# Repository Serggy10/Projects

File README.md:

# Projects
This folder contains projects I have been working on, including plans and designs in Autodesk Autocad and Inventor, PCB designs using Kicad, software development for Arduino/ESP32 using Visual Studio Code in C++, Android Studio and others.

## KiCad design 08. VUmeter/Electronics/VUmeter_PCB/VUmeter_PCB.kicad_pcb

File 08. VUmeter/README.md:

# Description
This project is based on the idea of a LED strip that reacts to sound. Controlled by an ESP32 and interacting with Alexa. Work in progress. Based on these ideas:

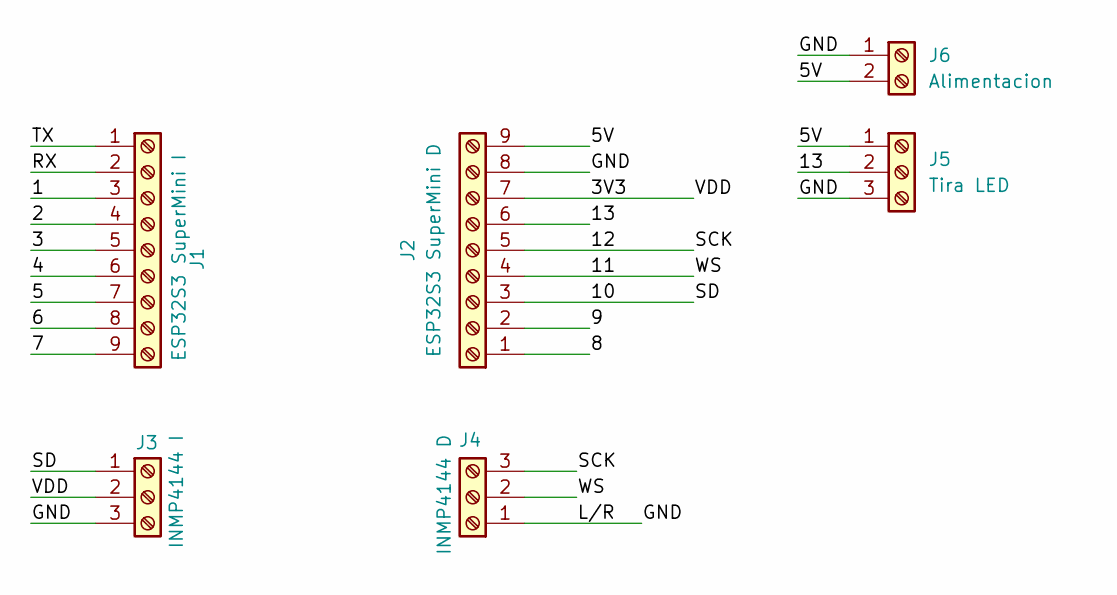
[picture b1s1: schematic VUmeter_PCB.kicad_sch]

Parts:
J1: ESP32S3 SuperMini I; PinHeader_1x09_P2.54mm_Vertical
J2: ESP32S3 SuperMini D; PinHeader_1x09_P2.54mm_Vertical
J3: INMP4144 I; PinHeader_1x03_P2.54mm_Vertical
J4: INMP4144 D; PinHeader_1x03_P2.54mm_Vertical
J5: Tira LED; PinHeader_1x03_P2.54mm_Vertical
J6: Alimentacion; PinHeader_1x02_P2.54mm_Vertical

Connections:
/1: J1.3
/2: J1.4
/3: J1.5
/3V3: J2.7, J3.2
/4: J1.6
/5: J1.7
/5V: J2.9, J5.1, J6.2
/6: J1.8
/7: J1.9
/8: J2.1
/9: J2.2
/10: J2.3, J3.1
/11: J2.4, J4.2
/12: J2.5, J4.3
/13: J2.6, J5.2
/GND: J2.8, J3.3, J4.1, J5.3, J6.1
/RX: J1.2
/TX: J1.1

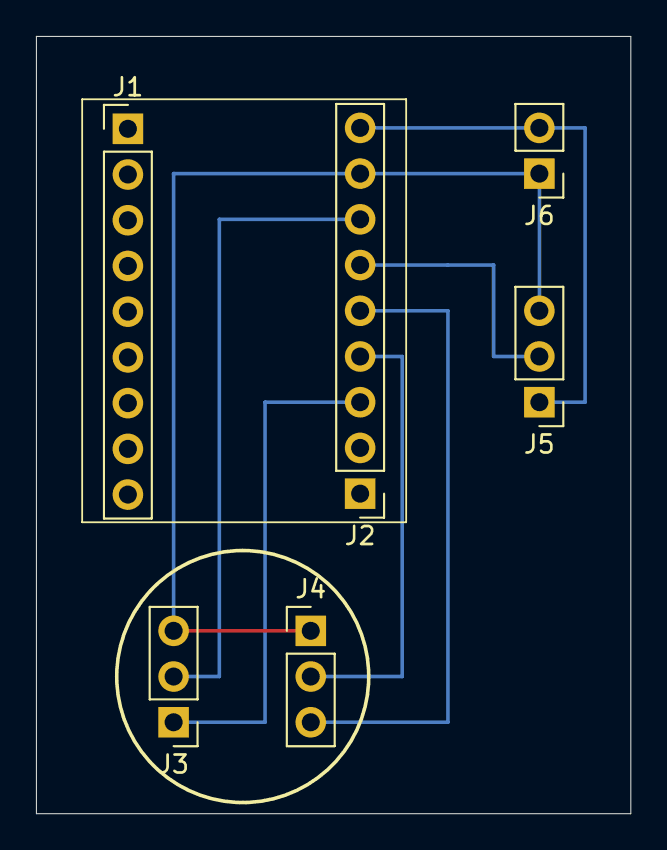
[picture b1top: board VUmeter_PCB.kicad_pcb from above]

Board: 2 copper layers, 33.0 x 43.2 mm, 6 parts (0 on the bottom side), 7 nets.

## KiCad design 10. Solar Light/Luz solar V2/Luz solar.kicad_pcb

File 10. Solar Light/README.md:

# Description IC
This project was born out of the poor quality of solar lights on the market. It uses a lithium-ion battery and a DW01A IC to manage the charge and discharge. The charging is done by a solar cell through a CN3163 IC. A video of it working can be found in the Resources folder. Work in progress.

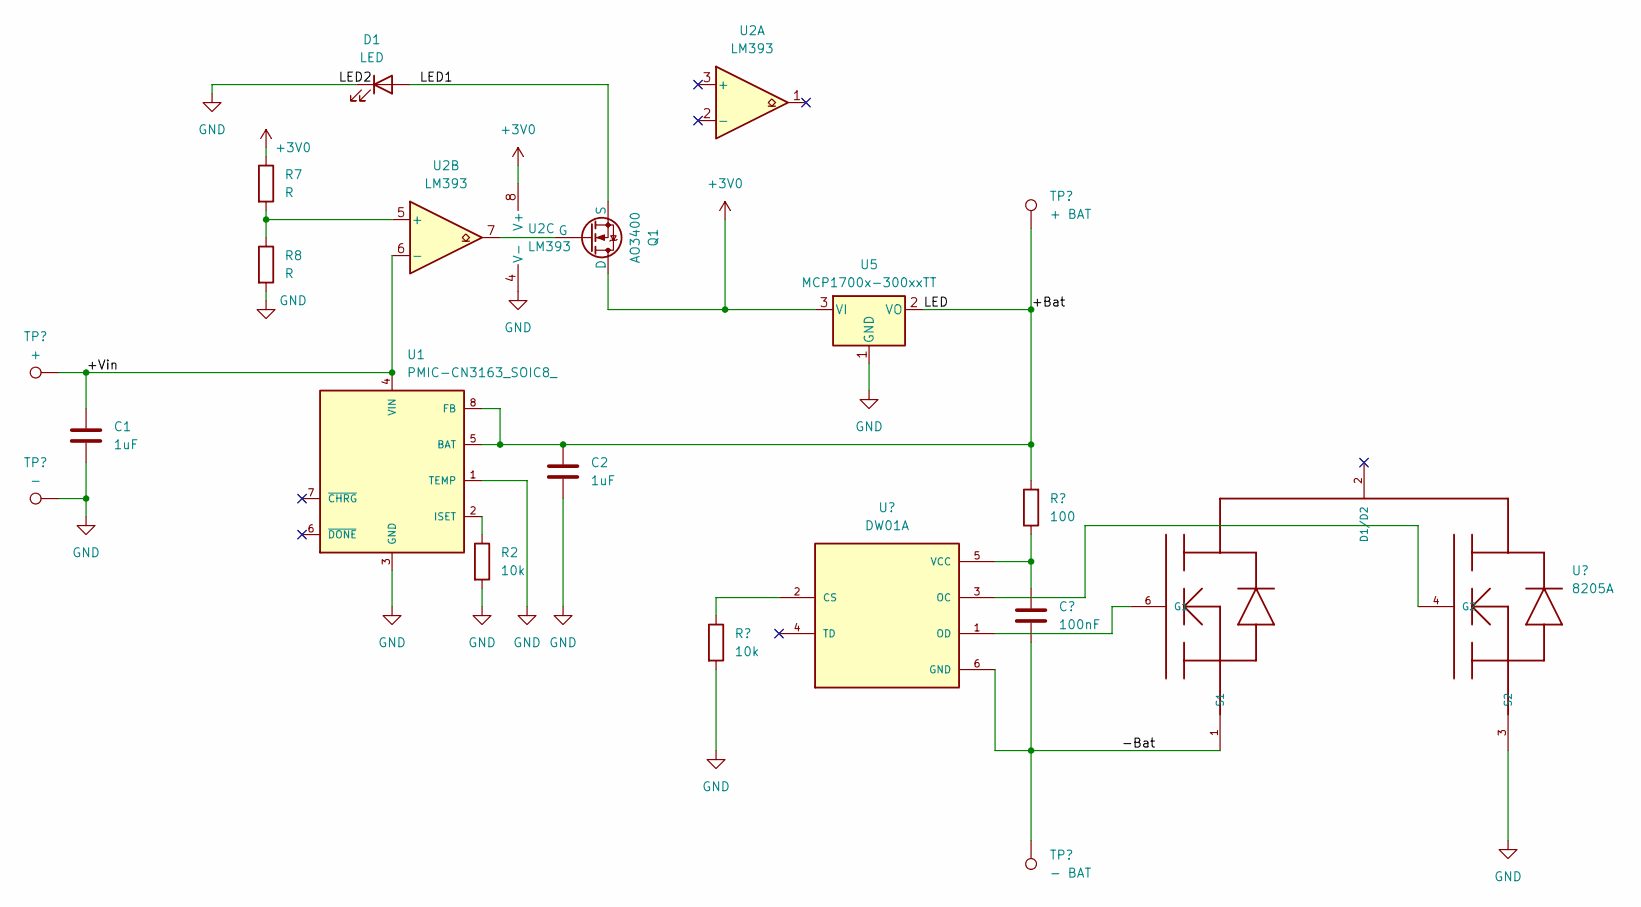
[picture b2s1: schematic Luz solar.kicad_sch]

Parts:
C1, C2: 1uF; C_1206_3216Metric
C3: 100nF; C_1206_3216Metric
D1: LED; LED_1W_3W_R8
Q1: AO3400; SOT-23
R2, R4: 10k; R_1206_3216Metric_Pad1.30x1.75mm_HandSolder
R5: 100; R_1206_3216Metric_Pad1.30x1.75mm_HandSolder
R7, R8: R; R_1206_3216Metric_Pad1.30x1.75mm_HandSolder
TP1: +; TestPoint_Pad_2.0x2.0mm
TP2: -; TestPoint_Pad_2.0x2.0mm
TP3: + BAT; TestPoint_Keystone_5019_Minature
TP4: - BAT; TestPoint_Keystone_5019_Minature
U1: PMIC-CN3163_SOIC8_; SOIC8-1.27-5X4MM; MPN CN3063
U2: LM393; SOP-8_5.28x5.23mm_P1.27mm
U3: DW01A; SOT95P280X145-6N; PARTREV 1.8
U4: 8205A; SOT-23-6_Handsoldering
U5: MCP1700x-300xxTT; SOT-23

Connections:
+3V0: Q1.1 (D), R7.1, U2.8 (V+), U5.3 (VI)
/+Bat: C2.1, R5.2, TP3.1, U1.5 (BAT), U1.8 (FB), U5.2 (VO)
/+Vin: C1.1, TP1.1, U1.4 (VIN), U2.6 (-)
/-Bat: C3.2, TP4.1, U3.6 (GND), U4.1 (S1)
/LED1: D1.2 (A), Q1.3 (S)
GND: C1.2, C2.2, D1.1 (K), R2.2, R4.2, R8.2, TP2.1, U1.1 (TEMP), U1.3 (GND), U2.4 (V-), U4.3 (S2), U5.1 (GND)
unnamed: Q1.2 (G), U2.7
unnamed: R2.1, U1.2 (ISET)
unnamed: R7.2, R8.1, U2.5 (+)
unnamed: R4.1, U3.2 (CS)
unnamed: U3.3 (OC), U4.4 (G2)
unnamed: U3.1 (OD), U4.6 (G1)
unnamed: C3.1, R5.1, U3.5 (VCC)

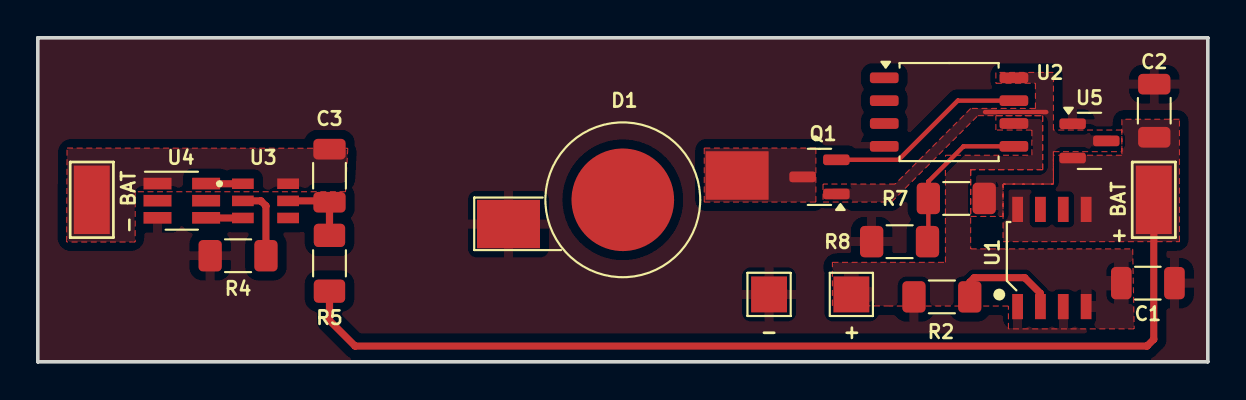
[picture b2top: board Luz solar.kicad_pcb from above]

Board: 2 copper layers, 65.0 x 18.0 mm, 19 parts (0 on the bottom side), 13 nets.

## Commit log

2024-12-25 Create Automatic_Feeder
    This folder contains several versions of an automatic feeder controlled by a microcontroller, programmed in C++, HTML and CSS.
2024-12-25 First upload of ComederoV6
2024-12-25 no message
2024-12-26 Removed directories
2024-12-26 Restore the ComederoV4 folder.
2024-12-28 Rename README.txt to README.md
2025-01-22 Up and down test with increasing and decreasing current
2025-01-23 Update of working manual mode and a test for automatic mode.
2025-01-23 Working automatic mode.
2025-01-24 12. Garage engine update. Introduced reduced speed at difererent ranges of Hall sensor. Introduced speed monitoring for security reasons.
2025-01-24 12. Garaje motor. Update with automatic saving of some parameters in case of shutdown.
2025-01-24 12. Garaje motor. Details update.
2025-01-26 12. Garage motor. New features and bug fixes.
2025-01-29 12. Garage Motor. General update.
2025-02-24 0.8 VUmeter. Progress update.
2025-02-25 08. VUmeter. Start PCB proyect.
2025-02-26 08.VUmeter. PCB update and Software update according to schematic.
2025-02-26 16. Protection catapult. Start of PCB schematic and layout.
2025-03-01 16. Protection catapult. Catapult first design.
2025-03-01 16. Protection catapult. Catapult first design update.
2025-03-02 16. Protection catapult. Dispenser update.
